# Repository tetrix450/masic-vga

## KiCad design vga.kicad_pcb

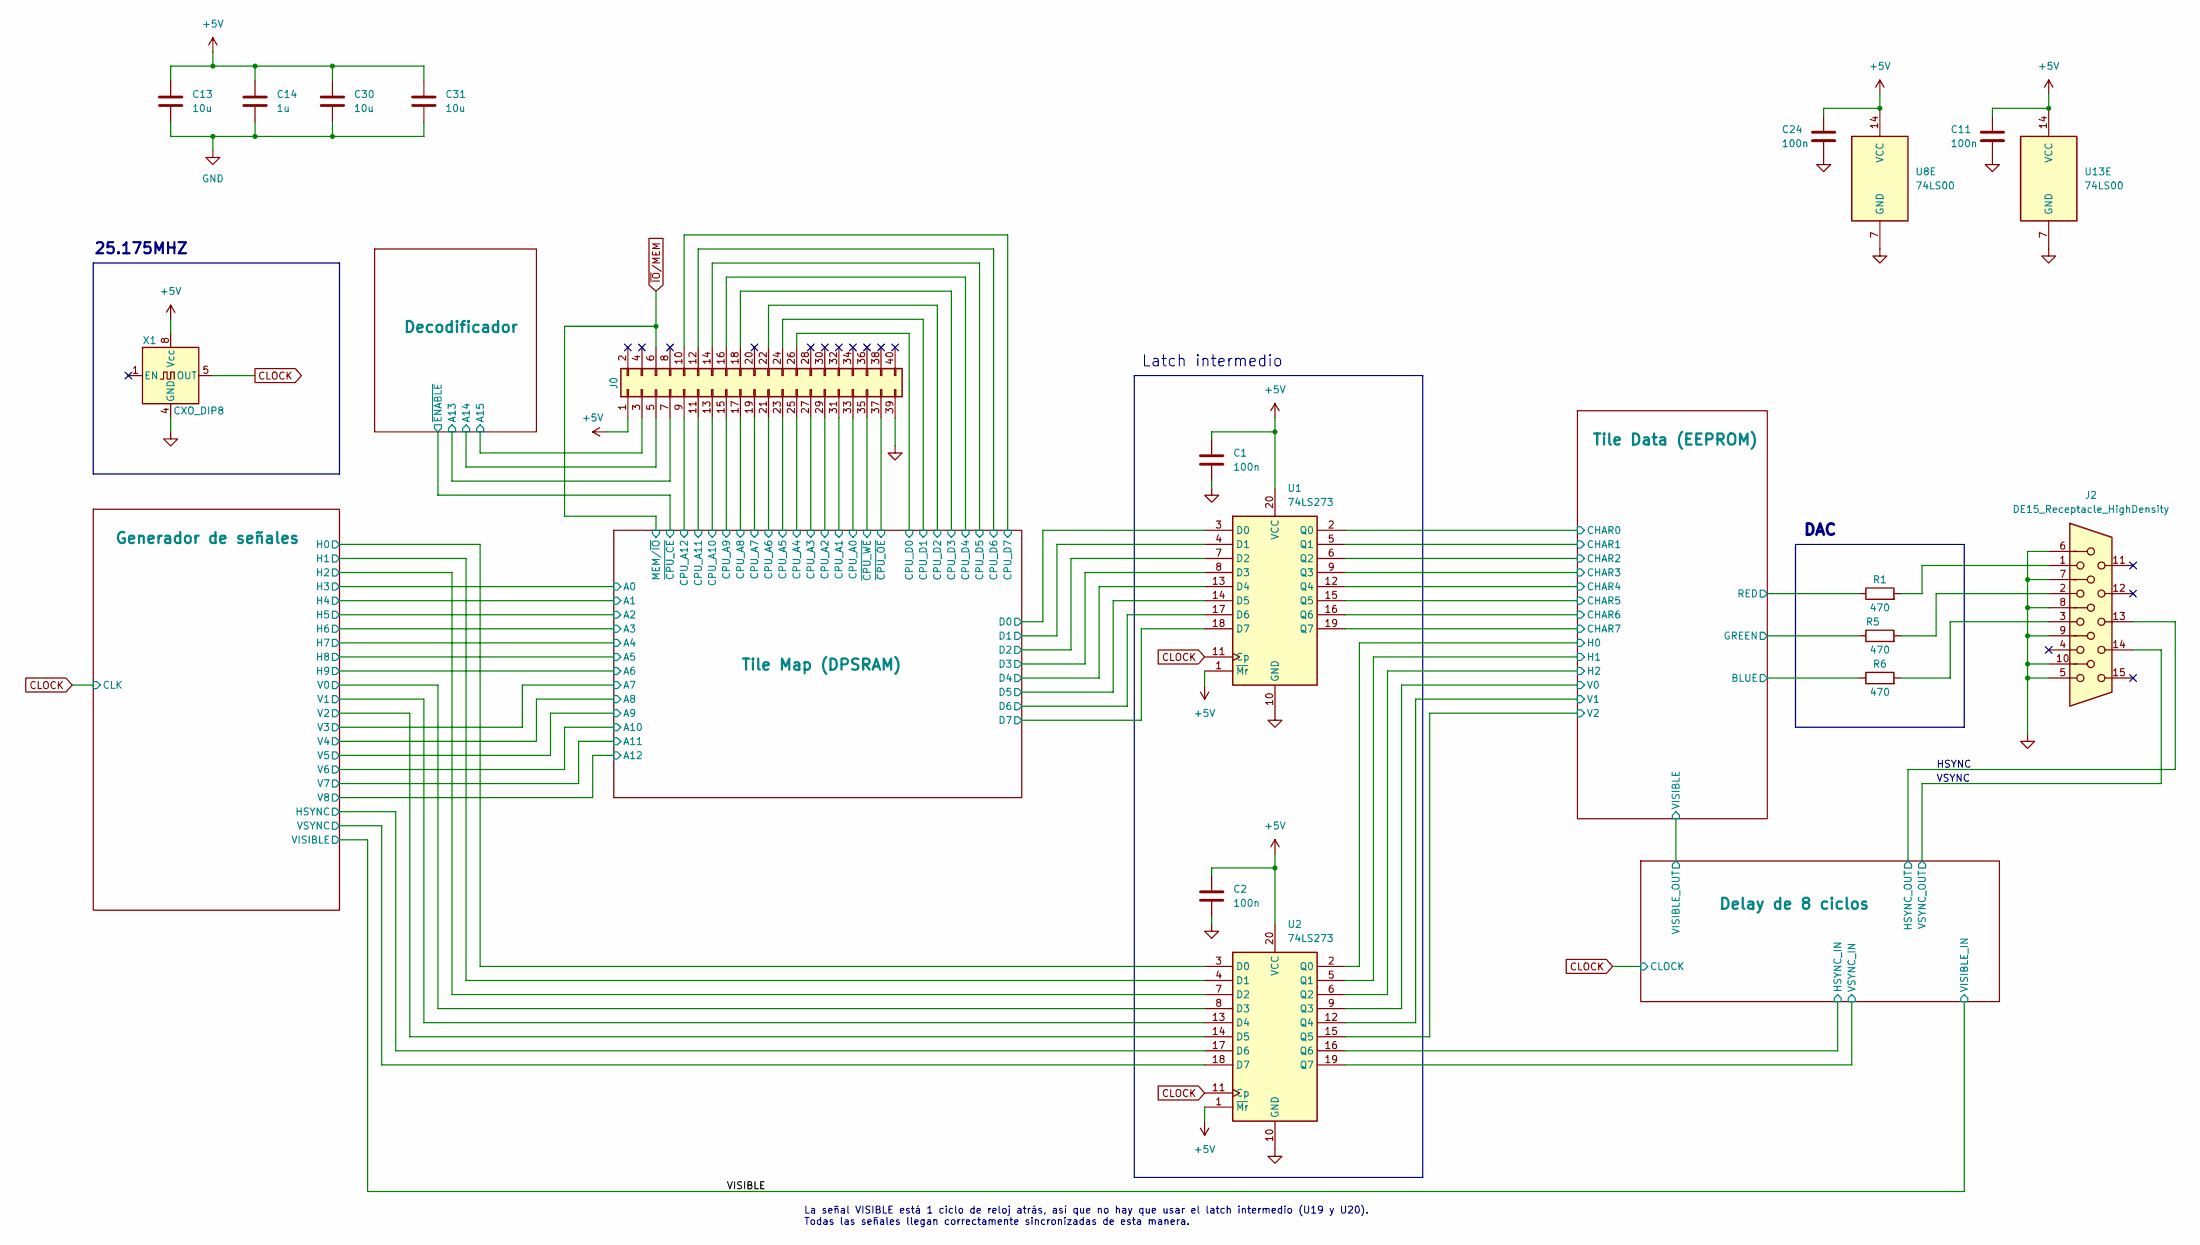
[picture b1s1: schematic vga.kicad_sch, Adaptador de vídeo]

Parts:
C1, C2, C11, C24: 100n; C_Disc_7.62mm
C13, C30, C31: 10u; C_Radial_D6.3mm_H5.0mm_P2.50mm
C14: 1u; C_Radial_D6.3mm_H5.0mm_P2.50mm
J0: Conn_02x20_Counter_Clockwise; PinSocket_2x20_P2.54mm_Vertical
J2: DE15_Receptacle_HighDensity; DSUB-15-HD_Female_Horizontal_P2.29x2.54mm_EdgePinOffset9.40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
R1, R5, R6: 470; R_Axial_DIN0207_L6.3mm_D2.5mm_P7.62mm_Horizontal
U1, U2: 74LS273; DIP-20_W7.62mm
U8, U13: 74LS00; DIP-14_W7.62mm
X1: CXO_DIP8; Oscillator_DIP-8

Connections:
+5V: C1.1, C2.1, C11.1, C13.1, C14.1, C24.1, C30.1, C31.1, U1.1 (~Mr), U1.20 (VCC), U2.1 (~Mr), U2.20 (VCC), U8.14 (VCC), U13.14 (VCC), X1.8 (Vcc); also elsewhere on the board
/Delay de 8 ciclos/HSYNC_IN: U2.16 (Q6); also elsewhere on the board
/Delay de 8 ciclos/HSYNC_OUT: J2.13; also elsewhere on the board
/Delay de 8 ciclos/VSYNC_IN: U2.19 (Q7); also elsewhere on the board
/Delay de 8 ciclos/VSYNC_OUT: J2.14; also elsewhere on the board
/Generador de señales/H0: U2.3 (D0); also elsewhere on the board
/Generador de señales/H1: U2.4 (D1); also elsewhere on the board
/Generador de señales/H2: U2.7 (D2); also elsewhere on the board
/Generador de señales/HSYNC: U2.17 (D6); also elsewhere on the board
/Generador de señales/HSYNC LATCH/Q: U8.8, U8.12; also elsewhere on the board
/Generador de señales/HSYNC LATCH/~Q: U8.10, U8.11; also elsewhere on the board
/Generador de señales/HSYNC LATCH/~R: U8.13; also elsewhere on the board
/Generador de señales/HSYNC LATCH/~S: U8.9; also elsewhere on the board
/Generador de señales/V0: U2.8 (D3); also elsewhere on the board
/Generador de señales/V1: U2.13 (D4); also elsewhere on the board
/Generador de señales/V2: U2.14 (D5); also elsewhere on the board
/Generador de señales/VSYNC: U2.18 (D7); also elsewhere on the board
/Generador de señales/VSYNC_LATCH/Q: U13.8, U13.12; also elsewhere on the board
/Generador de señales/VSYNC_LATCH/~Q: U13.10, U13.11; also elsewhere on the board
/Generador de señales/VSYNC_LATCH/~R: U13.13; also elsewhere on the board
/Generador de señales/VSYNC_LATCH/~S: U13.9; also elsewhere on the board
/Tile Data (EEPROM)/BLUE: R6.1; also elsewhere on the board
/Tile Data (EEPROM)/CHAR0: U1.2 (Q0); also elsewhere on the board
/Tile Data (EEPROM)/CHAR1: U1.5 (Q1); also elsewhere on the board
/Tile Data (EEPROM)/CHAR2: U1.6 (Q2); also elsewhere on the board
/Tile Data (EEPROM)/CHAR3: U1.9 (Q3); also elsewhere on the board
/Tile Data (EEPROM)/CHAR4: U1.12 (Q4); also elsewhere on the board
/Tile Data (EEPROM)/CHAR5: U1.15 (Q5); also elsewhere on the board
/Tile Data (EEPROM)/CHAR6: U1.16 (Q6); also elsewhere on the board
/Tile Data (EEPROM)/CHAR7: U1.19 (Q7); also elsewhere on the board
/Tile Data (EEPROM)/GREEN: R5.1; also elsewhere on the board
/Tile Data (EEPROM)/H0: U2.2 (Q0); also elsewhere on the board
/Tile Data (EEPROM)/H1: U2.5 (Q1); also elsewhere on the board
/Tile Data (EEPROM)/H2: U2.6 (Q2); also elsewhere on the board
/Tile Data (EEPROM)/RED: R1.1; also elsewhere on the board
/Tile Data (EEPROM)/V0: U2.9 (Q3); also elsewhere on the board
/Tile Data (EEPROM)/V1: U2.12 (Q4); also elsewhere on the board
/Tile Data (EEPROM)/V2: U2.15 (Q5); also elsewhere on the board
/Tile Map (DPSRAM)/D0: U1.3 (D0); also elsewhere on the board
/Tile Map (DPSRAM)/D1: U1.4 (D1); also elsewhere on the board
/Tile Map (DPSRAM)/D2: U1.7 (D2); also elsewhere on the board
/Tile Map (DPSRAM)/D3: U1.8 (D3); also elsewhere on the board
/Tile Map (DPSRAM)/D4: U1.13 (D4); also elsewhere on the board
/Tile Map (DPSRAM)/D5: U1.14 (D5); also elsewhere on the board
/Tile Map (DPSRAM)/D6: U1.17 (D6); also elsewhere on the board
/Tile Map (DPSRAM)/D7: U1.18 (D7); also elsewhere on the board
CLOCK: U1.11 (Cp), U2.11 (Cp), X1.5 (OUT); also elsewhere on the board
GND: C1.2, C2.2, C11.2, C13.2, C14.2, C24.2, C30.2, C31.2, J2.5, J2.6, J2.7, J2.8, J2.9, J2.10, U1.10 (GND), U2.10 (GND), U8.7 (GND), U13.7 (GND), X1.4 (GND); also elsewhere on the board
unnamed: J2.1, R1.2
unnamed: J2.2, R5.2
unnamed: J2.3, R6.2

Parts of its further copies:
J1: Conn_02x20_Counter_Clockwise; PinSocket_2x20_P2.54mm_Vertical

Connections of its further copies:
+5V: J1.1; also elsewhere on the board
/Decodificador/A13: J1.7; also elsewhere on the board
/Decodificador/A14: J1.5; also elsewhere on the board
/Decodificador/A15: J1.3; also elsewhere on the board
/Tile Map (DPSRAM)/CPU_A0: J1.33; also elsewhere on the board
/Tile Map (DPSRAM)/CPU_A1: J1.31; also elsewhere on the board
/Tile Map (DPSRAM)/CPU_A2: J1.29; also elsewhere on the board
/Tile Map (DPSRAM)/CPU_A3: J1.27; also elsewhere on the board
/Tile Map (DPSRAM)/CPU_A4: J1.25; also elsewhere on the board
/Tile Map (DPSRAM)/CPU_A5: J1.23; also elsewhere on the board
/Tile Map (DPSRAM)/CPU_A6: J1.21; also elsewhere on the board
/Tile Map (DPSRAM)/CPU_A7: J1.19; also elsewhere on the board
/Tile Map (DPSRAM)/CPU_A8: J1.17; also elsewhere on the board
/Tile Map (DPSRAM)/CPU_A9: J1.15; also elsewhere on the board
/Tile Map (DPSRAM)/CPU_A10: J1.13; also elsewhere on the board
/Tile Map (DPSRAM)/CPU_A11: J1.11; also elsewhere on the board
/Tile Map (DPSRAM)/CPU_A12: J1.9; also elsewhere on the board
/Tile Map (DPSRAM)/CPU_D0: J1.26; also elsewhere on the board
/Tile Map (DPSRAM)/CPU_D1: J1.24; also elsewhere on the board
/Tile Map (DPSRAM)/CPU_D2: J1.22; also elsewhere on the board
/Tile Map (DPSRAM)/CPU_D3: J1.18; also elsewhere on the board
/Tile Map (DPSRAM)/CPU_D4: J1.16; also elsewhere on the board
/Tile Map (DPSRAM)/CPU_D5: J1.14; also elsewhere on the board
/Tile Map (DPSRAM)/CPU_D6: J1.12; also elsewhere on the board
/Tile Map (DPSRAM)/CPU_D7: J1.10; also elsewhere on the board
/Tile Map (DPSRAM)/~CPU_OE: J1.37; also elsewhere on the board
/Tile Map (DPSRAM)/~CPU_WE: J1.35; also elsewhere on the board
GND: J1.39; also elsewhere on the board
~IO/MEM: J1.6; also elsewhere on the board

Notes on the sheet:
25.175MHZ
Latch intermedio
HSYNC
VSYNC
DAC
La señal VISIBLE está 1 ciclo de reloj atrás, así que no hay que usar el latch intermedio (U19 y U20). Todas las señales llegan correctamente sincronizadas de esta manera.

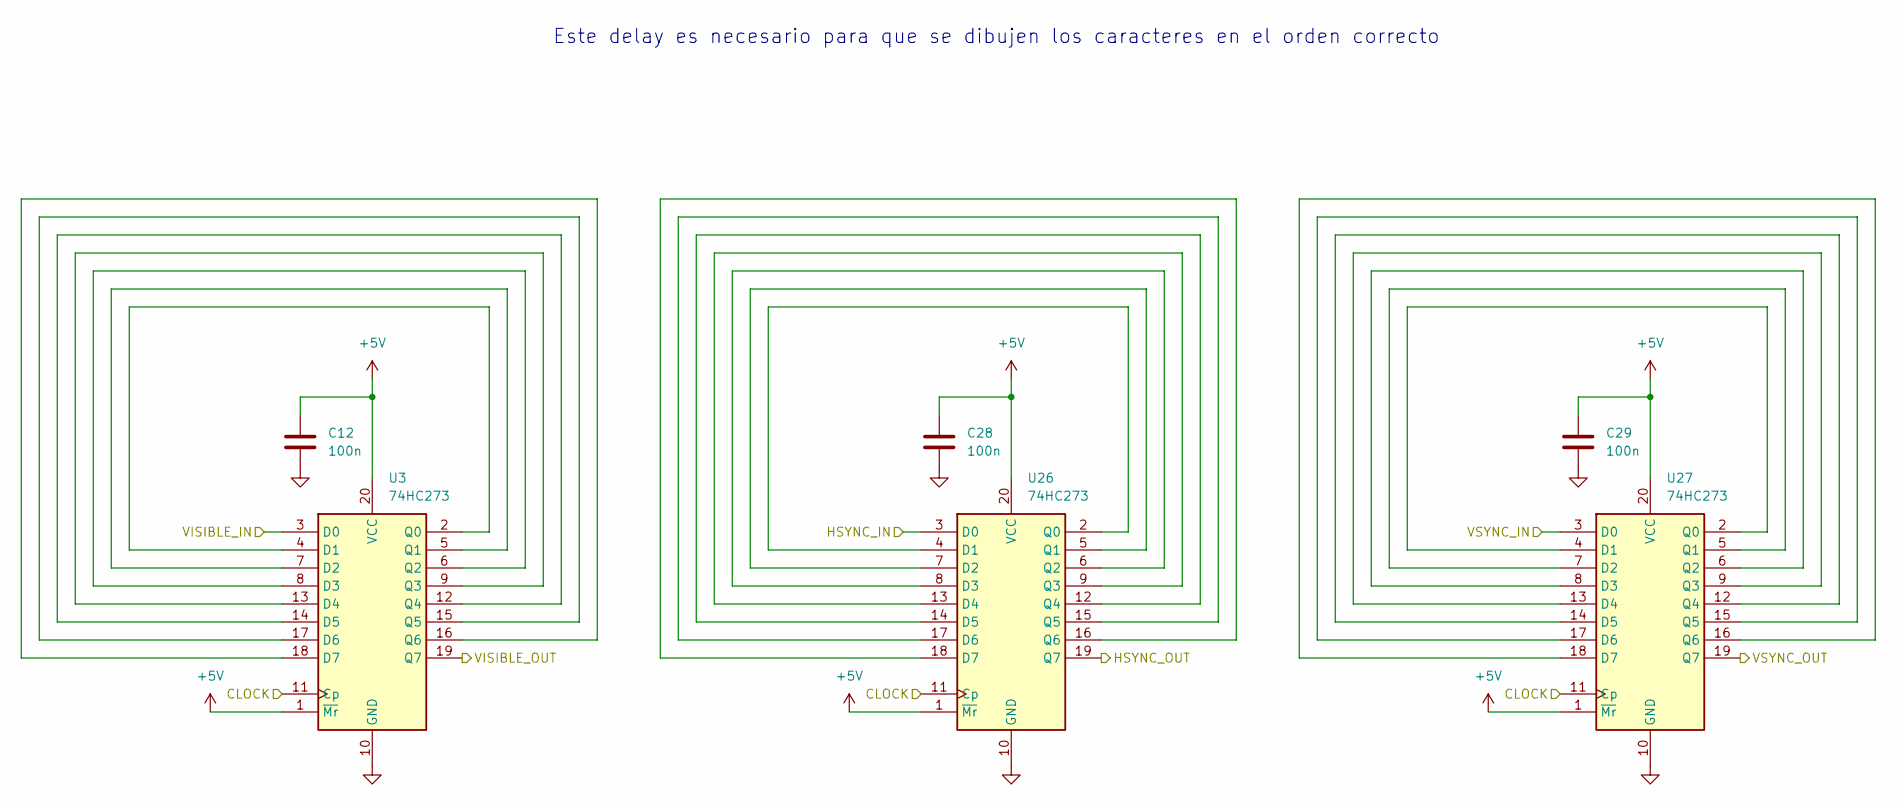
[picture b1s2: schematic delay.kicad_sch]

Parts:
C12, C28, C29: 100n; C_Disc_7.62mm
U3, U26, U27: 74HC273; DIP-20_W7.62mm

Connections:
+5V: C12.1, C28.1, C29.1, U3.1 (~Mr), U3.20 (VCC), U26.1 (~Mr), U26.20 (VCC), U27.1 (~Mr), U27.20 (VCC); also elsewhere on the board
/Delay de 8 ciclos/HSYNC_IN: U26.3 (D0); also elsewhere on the board
/Delay de 8 ciclos/HSYNC_OUT: U26.19 (Q7); also elsewhere on the board
/Delay de 8 ciclos/VISIBLE_OUT: U3.19 (Q7); also elsewhere on the board
/Delay de 8 ciclos/VSYNC_IN: U27.3 (D0); also elsewhere on the board
/Delay de 8 ciclos/VSYNC_OUT: U27.19 (Q7); also elsewhere on the board
/VISIBLE: U3.3 (D0); also elsewhere on the board
CLOCK: U3.11 (Cp), U26.11 (Cp), U27.11 (Cp); also elsewhere on the board
GND: C12.2, C28.2, C29.2, U3.10 (GND), U26.10 (GND), U27.10 (GND); also elsewhere on the board
unnamed: U3.2 (Q0), U3.4 (D1)
unnamed: U3.5 (Q1), U3.7 (D2)
unnamed: U3.6 (Q2), U3.8 (D3)
unnamed: U3.9 (Q3), U3.13 (D4)
unnamed: U3.12 (Q4), U3.14 (D5)
unnamed: U3.15 (Q5), U3.17 (D6)
unnamed: U3.16 (Q6), U3.18 (D7)
unnamed: U26.2 (Q0), U26.4 (D1)
unnamed: U26.5 (Q1), U26.7 (D2)
unnamed: U26.6 (Q2), U26.8 (D3)
unnamed: U26.9 (Q3), U26.13 (D4)
unnamed: U26.12 (Q4), U26.14 (D5)
unnamed: U26.15 (Q5), U26.17 (D6)
unnamed: U26.16 (Q6), U26.18 (D7)
unnamed: U27.2 (Q0), U27.4 (D1)
unnamed: U27.5 (Q1), U27.7 (D2)
unnamed: U27.6 (Q2), U27.8 (D3)
unnamed: U27.9 (Q3), U27.13 (D4)
unnamed: U27.12 (Q4), U27.14 (D5)
unnamed: U27.15 (Q5), U27.17 (D6)
unnamed: U27.16 (Q6), U27.18 (D7)

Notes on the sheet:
Este delay es necesario para que se dibujen los caracteres en el orden correcto

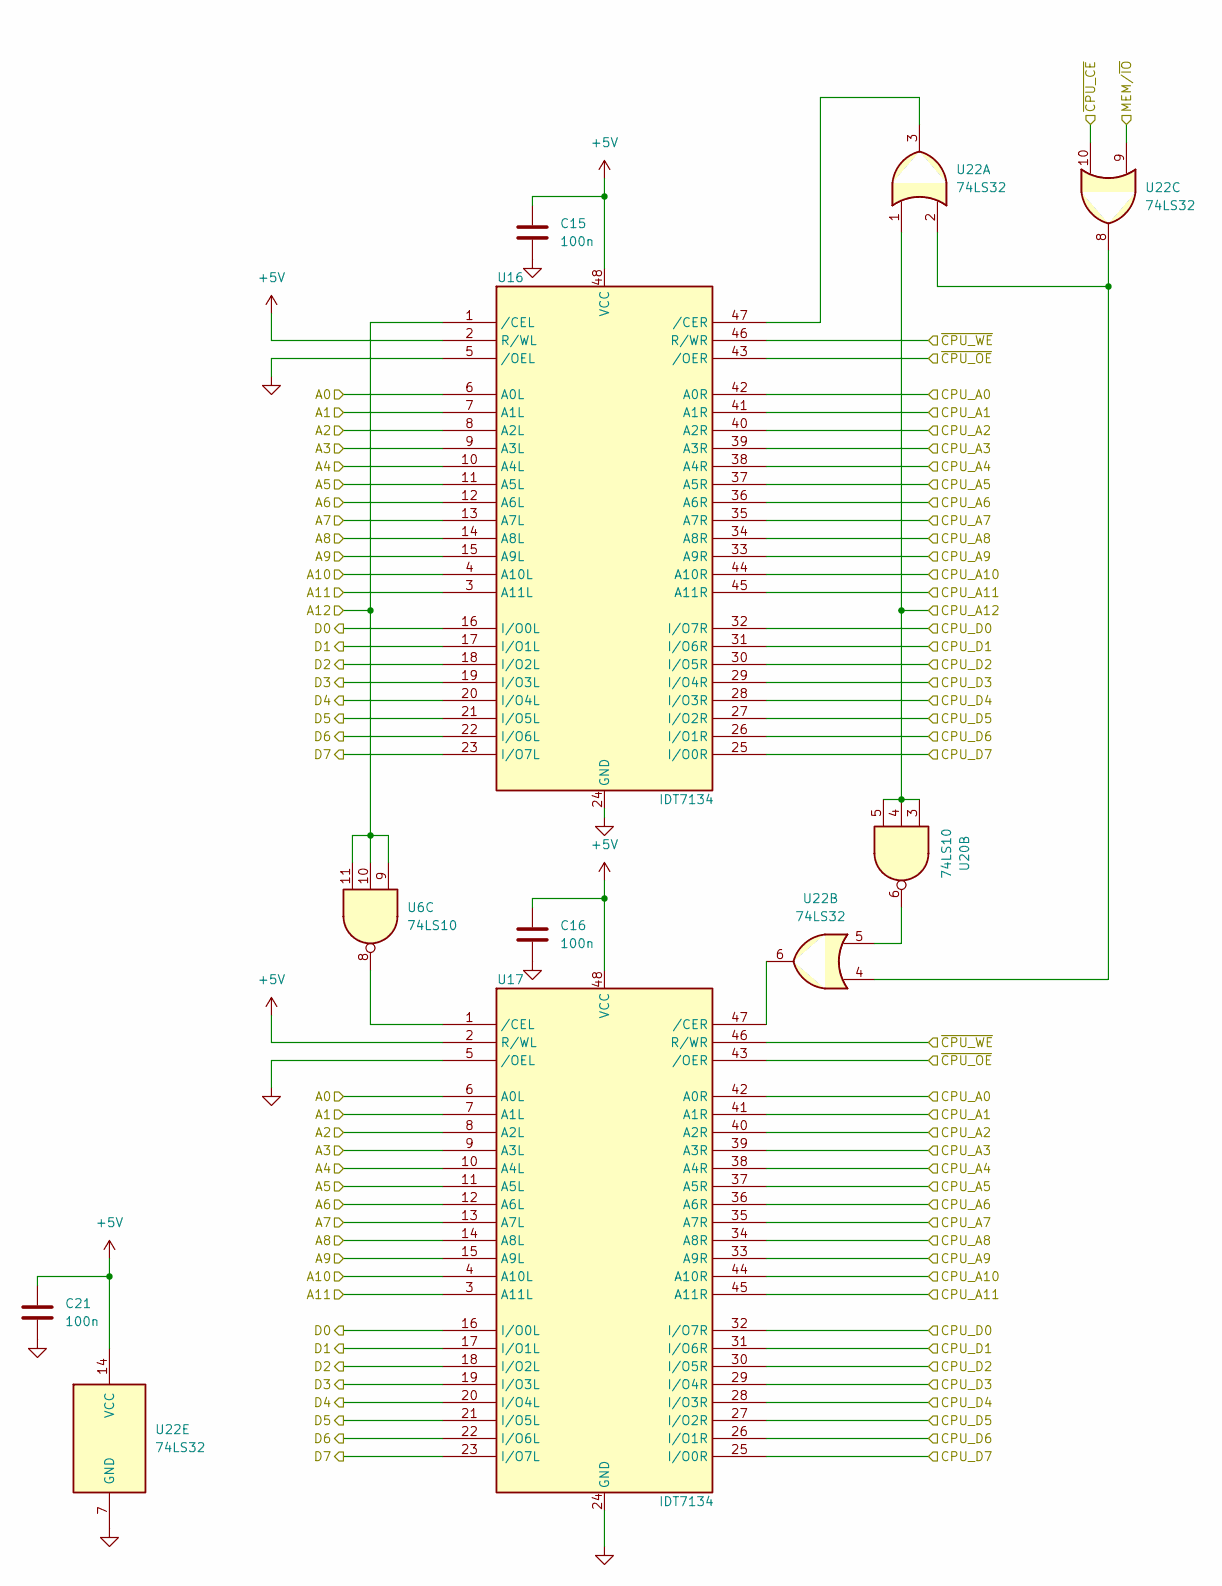
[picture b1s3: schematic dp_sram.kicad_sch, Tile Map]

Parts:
C15, C16, C21: 100n; C_Disc_7.62mm
U6, U20: 74LS10; DIP-14_W7.62mm
U16, U17: IDT7134; DIP-48_W15.24mm
U22: 74LS32; DIP-14_W7.62mm

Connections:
+5V: C15.1, C16.1, C21.1, U16.2 (R/WL), U16.48 (VCC), U17.2 (R/WL), U17.48 (VCC), U22.14 (VCC); also elsewhere on the board
/Decodificador/~ENABLE: U22.10; also elsewhere on the board
/Generador de señales/H3: U16.6 (A0L), U17.6 (A0L); also elsewhere on the board
/Generador de señales/H4: U16.7 (A1L), U17.7 (A1L); also elsewhere on the board
/Generador de señales/H5: U16.8 (A2L), U17.8 (A2L); also elsewhere on the board
/Generador de señales/H6: U16.9 (A3L), U17.9 (A3L); also elsewhere on the board
/Generador de señales/H7: U16.10 (A4L), U17.10 (A4L); also elsewhere on the board
/Generador de señales/H8: U16.11 (A5L), U17.11 (A5L); also elsewhere on the board
/Generador de señales/H9: U16.12 (A6L), U17.12 (A6L); also elsewhere on the board
/Generador de señales/V3: U16.13 (A7L), U17.13 (A7L); also elsewhere on the board
/Generador de señales/V4: U16.14 (A8L), U17.14 (A8L); also elsewhere on the board
/Generador de señales/V5: U16.15 (A9L), U17.15 (A9L); also elsewhere on the board
/Generador de señales/V6: U16.4 (A10L), U17.4 (A10L); also elsewhere on the board
/Generador de señales/V7: U16.3 (A11L), U17.3 (A11L); also elsewhere on the board
/Generador de señales/V8: U6.9, U6.10, U6.11, U16.1 (/CEL); also elsewhere on the board
/Tile Map (DPSRAM)/CPU_A0: U16.42 (A0R), U17.42 (A0R); also elsewhere on the board
/Tile Map (DPSRAM)/CPU_A1: U16.41 (A1R), U17.41 (A1R); also elsewhere on the board
/Tile Map (DPSRAM)/CPU_A2: U16.40 (A2R), U17.40 (A2R); also elsewhere on the board
/Tile Map (DPSRAM)/CPU_A3: U16.39 (A3R), U17.39 (A3R); also elsewhere on the board
/Tile Map (DPSRAM)/CPU_A4: U16.38 (A4R), U17.38 (A4R); also elsewhere on the board
/Tile Map (DPSRAM)/CPU_A5: U16.37 (A5R), U17.37 (A5R); also elsewhere on the board
/Tile Map (DPSRAM)/CPU_A6: U16.36 (A6R), U17.36 (A6R); also elsewhere on the board
/Tile Map (DPSRAM)/CPU_A7: U16.35 (A7R), U17.35 (A7R); also elsewhere on the board
/Tile Map (DPSRAM)/CPU_A8: U16.34 (A8R), U17.34 (A8R); also elsewhere on the board
/Tile Map (DPSRAM)/CPU_A9: U16.33 (A9R), U17.33 (A9R); also elsewhere on the board
/Tile Map (DPSRAM)/CPU_A10: U16.44 (A10R), U17.44 (A10R); also elsewhere on the board
/Tile Map (DPSRAM)/CPU_A11: U16.45 (A11R), U17.45 (A11R); also elsewhere on the board
/Tile Map (DPSRAM)/CPU_A12: U20.3, U20.4, U20.5, U22.1; also elsewhere on the board
/Tile Map (DPSRAM)/CPU_D0: U16.32 (I/O7R), U17.32 (I/O7R); also elsewhere on the board
/Tile Map (DPSRAM)/CPU_D1: U16.31 (I/O6R), U17.31 (I/O6R); also elsewhere on the board
/Tile Map (DPSRAM)/CPU_D2: U16.30 (I/O5R), U17.30 (I/O5R); also elsewhere on the board
/Tile Map (DPSRAM)/CPU_D3: U16.29 (I/O4R), U17.29 (I/O4R); also elsewhere on the board
/Tile Map (DPSRAM)/CPU_D4: U16.28 (I/O3R), U17.28 (I/O3R); also elsewhere on the board
/Tile Map (DPSRAM)/CPU_D5: U16.27 (I/O2R), U17.27 (I/O2R); also elsewhere on the board
/Tile Map (DPSRAM)/CPU_D6: U16.26 (I/O1R), U17.26 (I/O1R); also elsewhere on the board
/Tile Map (DPSRAM)/CPU_D7: U16.25 (I/O0R), U17.25 (I/O0R); also elsewhere on the board
/Tile Map (DPSRAM)/D0: U16.16 (I/O0L), U17.16 (I/O0L); also elsewhere on the board
/Tile Map (DPSRAM)/D1: U16.17 (I/O1L), U17.17 (I/O1L); also elsewhere on the board
/Tile Map (DPSRAM)/D2: U16.18 (I/O2L), U17.18 (I/O2L); also elsewhere on the board
/Tile Map (DPSRAM)/D3: U16.19 (I/O3L), U17.19 (I/O3L); also elsewhere on the board
/Tile Map (DPSRAM)/D4: U16.20 (I/O4L), U17.20 (I/O4L); also elsewhere on the board
/Tile Map (DPSRAM)/D5: U16.21 (I/O5L), U17.21 (I/O5L); also elsewhere on the board
/Tile Map (DPSRAM)/D6: U16.22 (I/O6L), U17.22 (I/O6L); also elsewhere on the board
/Tile Map (DPSRAM)/D7: U16.23 (I/O7L), U17.23 (I/O7L); also elsewhere on the board
/Tile Map (DPSRAM)/~CPU_OE: U16.43 (/OER), U17.43 (/OER); also elsewhere on the board
/Tile Map (DPSRAM)/~CPU_WE: U16.46 (R/WR), U17.46 (R/WR); also elsewhere on the board
GND: C15.2, C16.2, C21.2, U16.5 (/OEL), U16.24 (GND), U17.5 (/OEL), U17.24 (GND), U22.7 (GND); also elsewhere on the board
unnamed: U16.47 (/CER), U22.3
unnamed: U6.8, U17.1 (/CEL)
unnamed: U17.47 (/CER), U22.6
unnamed: U20.6, U22.5
unnamed: U22.2, U22.4, U22.8
~IO/MEM: U22.9; also elsewhere on the board

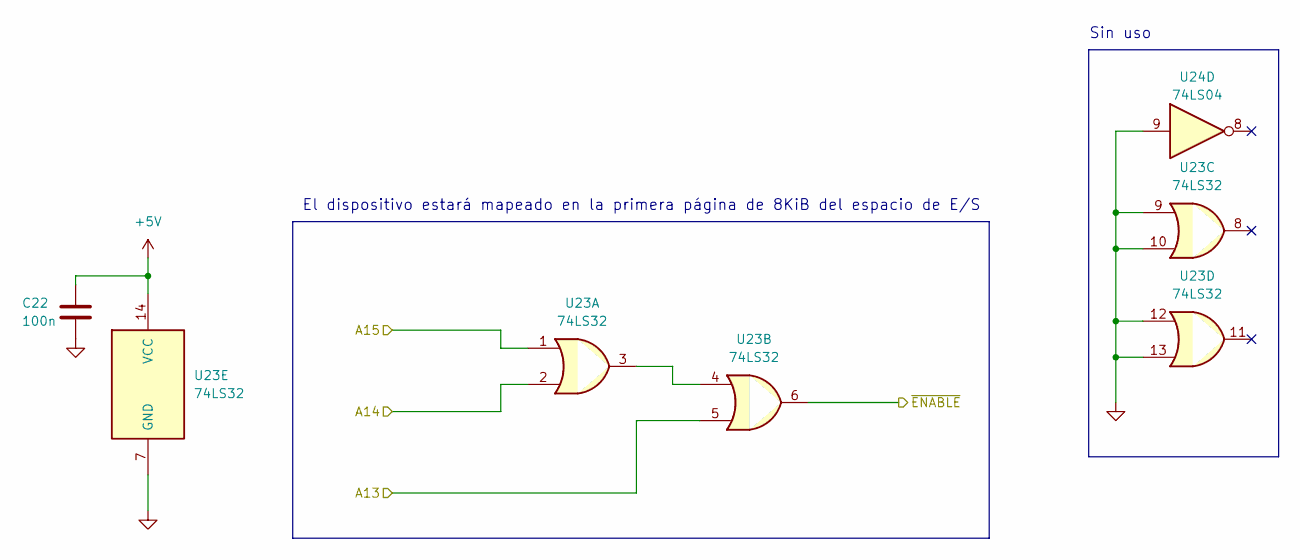
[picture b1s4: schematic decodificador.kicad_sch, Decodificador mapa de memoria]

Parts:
C22: 100n; C_Disc_7.62mm
U23: 74LS32; DIP-14_W7.62mm
U24: 74LS04; DIP-14_W7.62mm

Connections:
+5V: C22.1, U23.14 (VCC); also elsewhere on the board
/Decodificador/A13: U23.5; also elsewhere on the board
/Decodificador/A14: U23.2; also elsewhere on the board
/Decodificador/A15: U23.1; also elsewhere on the board
/Decodificador/~ENABLE: U23.6; also elsewhere on the board
GND: C22.2, U23.7 (GND), U23.9, U23.10, U23.12, U23.13, U24.9; also elsewhere on the board
unnamed: U23.3, U23.4

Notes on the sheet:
Sin uso
El dispositivo estará mapeado en la primera página de 8KiB del espacio de E/S

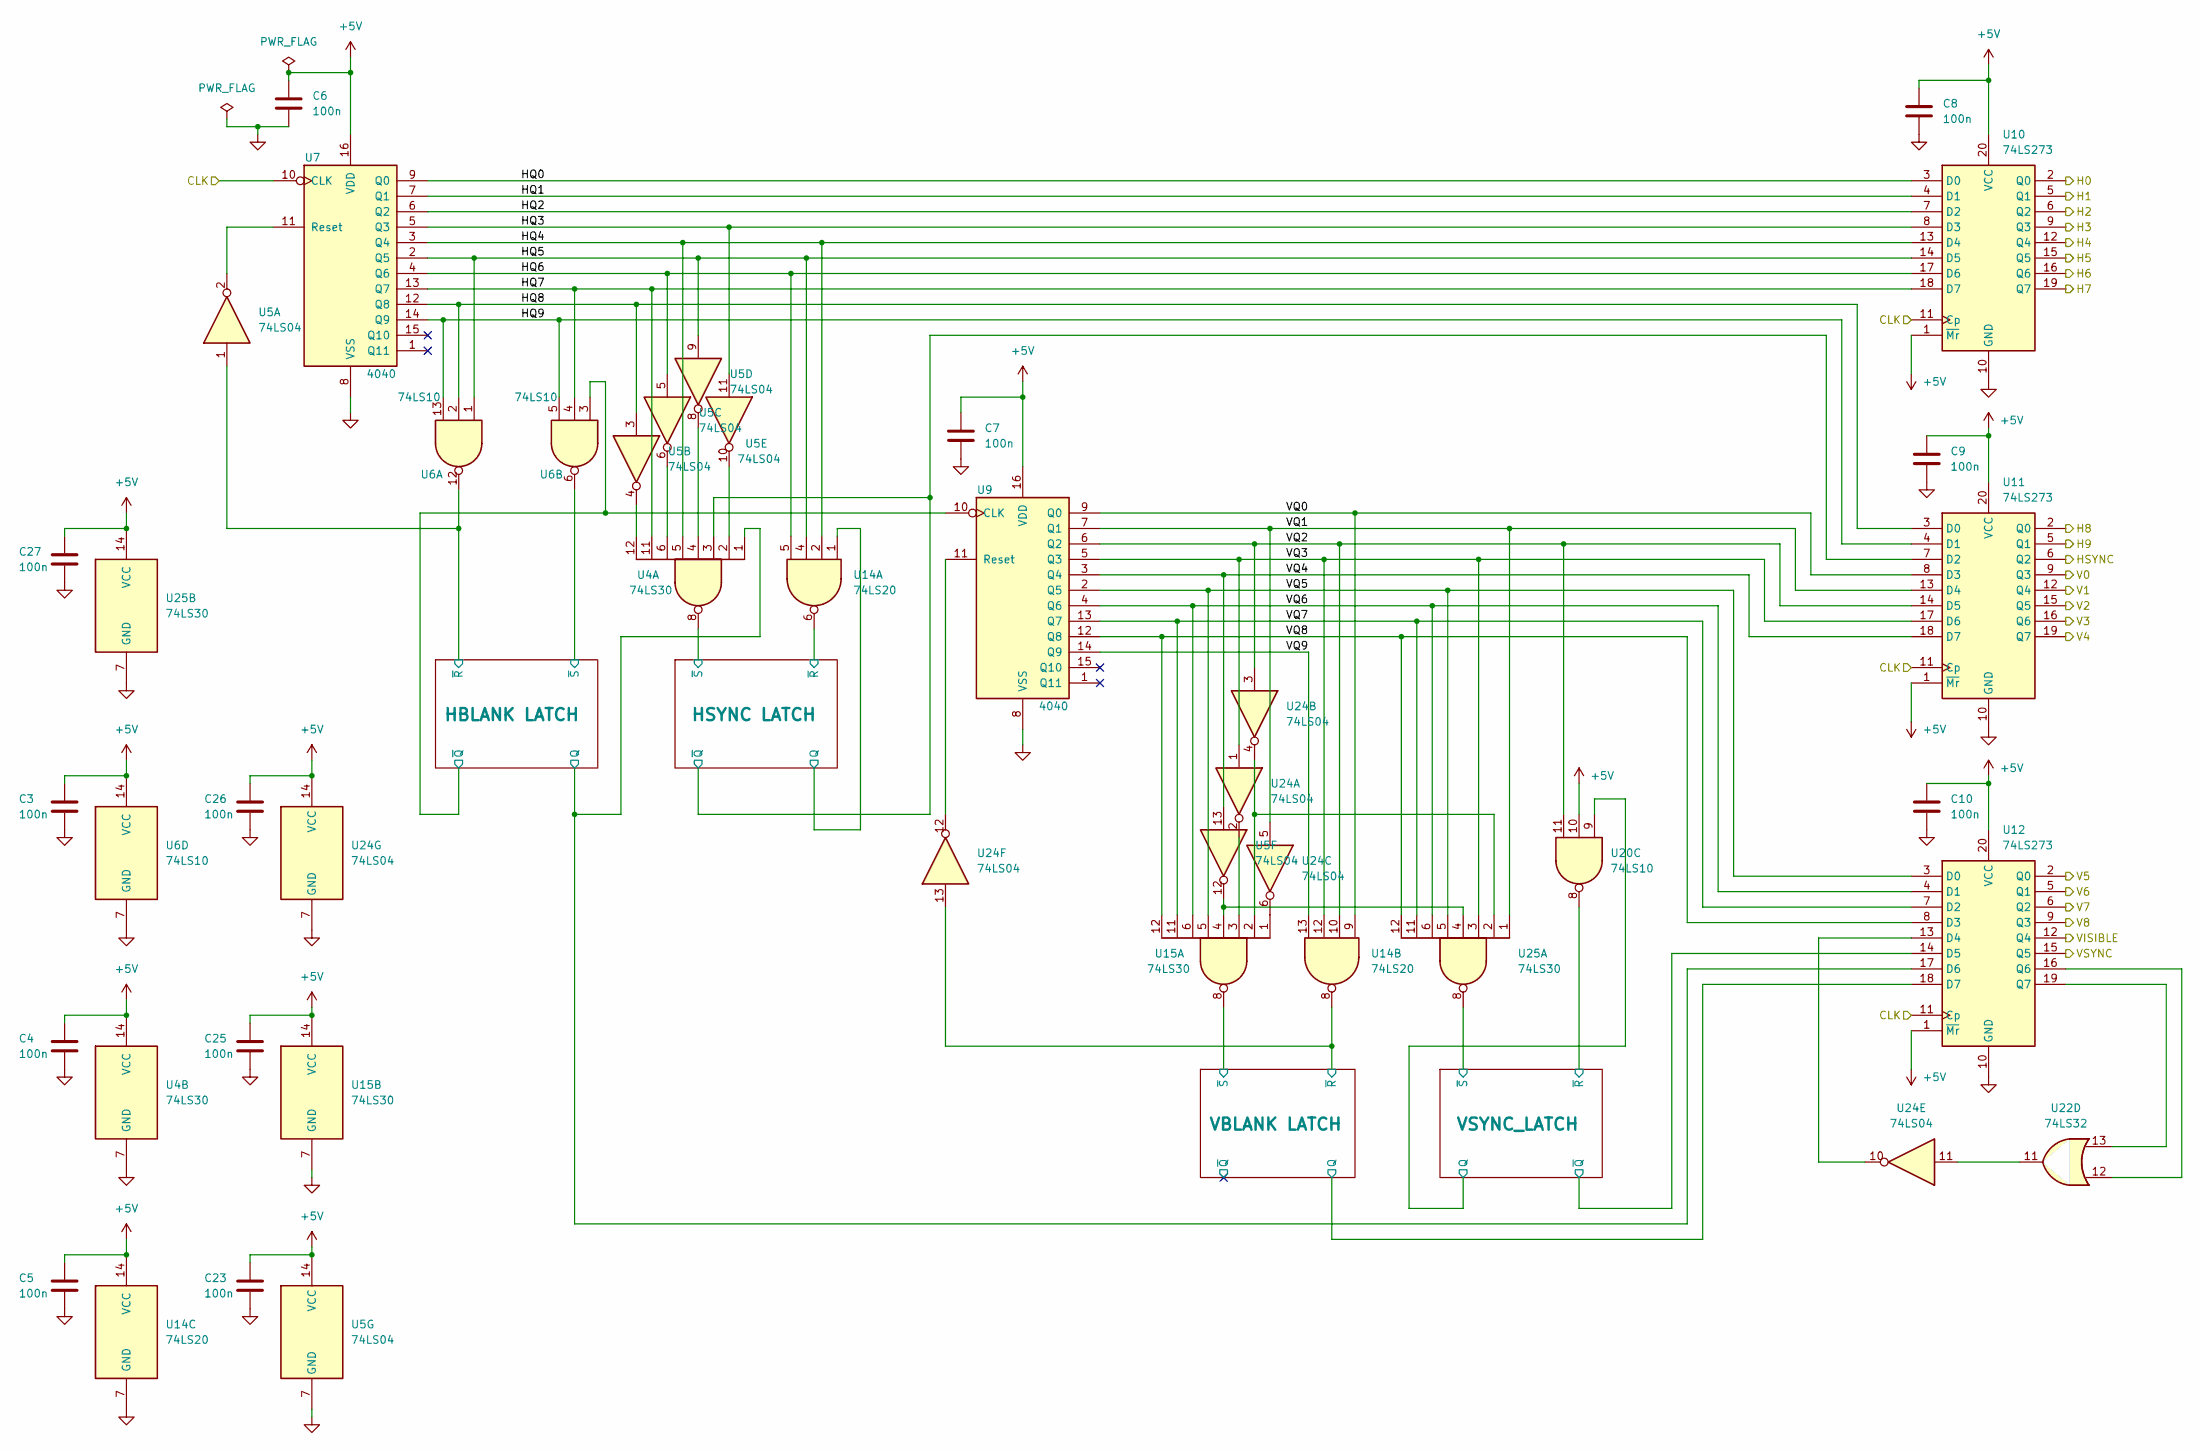
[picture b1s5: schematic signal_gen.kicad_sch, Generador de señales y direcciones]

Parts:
C3, C4, C5, C6, C7, C8, C9, C10, C23, C25, C26, C27: 100n; C_Disc_7.62mm
U4, U15, U25: 74LS30; DIP-14_W7.62mm
U5, U24: 74LS04; DIP-14_W7.62mm
U6, U20: 74LS10; DIP-14_W7.62mm
U7, U9: 4040; DIP-16_W7.62mm
U10, U11, U12: 74LS273; DIP-20_W7.62mm
U14: 74LS20; DIP-14_W7.62mm
U22: 74LS32; DIP-14_W7.62mm

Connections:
+5V: C3.1, C4.1, C5.1, C6.1, C7.1, C8.1, C9.1, C10.1, C23.1, C25.1, C26.1, C27.1, U4.14 (VCC), U5.14 (VCC), U6.14 (VCC), U7.16 (VDD), U9.16 (VDD), U10.1 (~Mr), U10.20 (VCC), U11.1 (~Mr), U11.20 (VCC), U12.1 (~Mr), U12.20 (VCC), U14.14 (VCC), U15.14 (VCC), U20.10, U24.14 (VCC), U25.14 (VCC); also elsewhere on the board
/Generador de señales/H0: U10.2 (Q0); also elsewhere on the board
/Generador de señales/H1: U10.5 (Q1); also elsewhere on the board
/Generador de señales/H2: U10.6 (Q2); also elsewhere on the board
/Generador de señales/H3: U10.9 (Q3); also elsewhere on the board
/Generador de señales/H4: U10.12 (Q4); also elsewhere on the board
/Generador de señales/H5: U10.15 (Q5); also elsewhere on the board
/Generador de señales/H6: U10.16 (Q6); also elsewhere on the board
/Generador de señales/H7: U10.19 (Q7); also elsewhere on the board
/Generador de señales/H8: U11.2 (Q0); also elsewhere on the board
/Generador de señales/H9: U11.5 (Q1); also elsewhere on the board
/Generador de señales/HBLANK LATCH/Q: U4.1, U12.17 (D6); also elsewhere on the board
/Generador de señales/HBLANK LATCH/~Q: U6.3, U9.10 (CLK); also elsewhere on the board
/Generador de señales/HBLANK LATCH/~R: U5.1, U6.12; also elsewhere on the board
/Generador de señales/HBLANK LATCH/~S: U6.6; also elsewhere on the board
/Generador de señales/HQ0: U7.9 (Q0), U10.3 (D0)
/Generador de señales/HQ1: U7.7 (Q1), U10.4 (D1)
/Generador de señales/HQ2: U7.6 (Q2), U10.7 (D2)
/Generador de señales/HQ3: U5.11, U7.5 (Q3), U10.8 (D3)
/Generador de señales/HQ4: U4.5, U7.3 (Q4), U10.13 (D4), U14.2
/Generador de señales/HQ5: U5.9, U6.1, U7.2 (Q5), U10.14 (D5), U14.4
/Generador de señales/HQ6: U5.5, U7.4 (Q6), U10.17 (D6), U14.5
/Generador de señales/HQ7: U4.11, U6.4, U7.13 (Q7), U10.18 (D7)
/Generador de señales/HQ8: U5.3, U6.2, U7.12 (Q8), U11.3 (D0)
/Generador de señales/HQ9: U6.5, U6.13, U7.14 (Q9), U11.4 (D1)
/Generador de señales/HSYNC: U11.6 (Q2); also elsewhere on the board
/Generador de señales/HSYNC LATCH/Q: U14.1; also elsewhere on the board
/Generador de señales/HSYNC LATCH/~Q: U4.3, U11.7 (D2); also elsewhere on the board
/Generador de señales/HSYNC LATCH/~R: U14.6; also elsewhere on the board
/Generador de señales/HSYNC LATCH/~S: U4.8; also elsewhere on the board
/Generador de señales/V0: U11.9 (Q3); also elsewhere on the board
/Generador de señales/V1: U11.12 (Q4); also elsewhere on the board
/Generador de señales/V2: U11.15 (Q5); also elsewhere on the board
/Generador de señales/V3: U11.16 (Q6); also elsewhere on the board
/Generador de señales/V4: U11.19 (Q7); also elsewhere on the board
/Generador de señales/V5: U12.2 (Q0); also elsewhere on the board
/Generador de señales/V6: U12.5 (Q1); also elsewhere on the board
/Generador de señales/V7: U12.6 (Q2); also elsewhere on the board
/Generador de señales/V8: U12.9 (Q3); also elsewhere on the board
/Generador de señales/VBLANK LATCH/Q: U12.18 (D7); also elsewhere on the board
/Generador de señales/VBLANK LATCH/~R: U14.8, U24.13; also elsewhere on the board
/Generador de señales/VBLANK LATCH/~S: U15.8; also elsewhere on the board
/Generador de señales/VQ0: U9.9 (Q0), U11.8 (D3), U14.9
/Generador de señales/VQ1: U9.7 (Q1), U11.13 (D4), U24.5, U25.1
/Generador de señales/VQ2: U9.6 (Q2), U11.14 (D5), U14.10, U20.11, U24.3
/Generador de señales/VQ3: U9.5 (Q3), U11.17 (D6), U14.12, U24.1, U25.3
/Generador de señales/VQ4: U5.13, U9.3 (Q4), U11.18 (D7)
/Generador de señales/VQ5: U9.2 (Q5), U12.3 (D0), U15.5, U25.5
/Generador de señales/VQ6: U9.4 (Q6), U12.4 (D1), U15.6, U25.6
/Generador de señales/VQ7: U9.13 (Q7), U12.7 (D2), U15.11, U25.11
/Generador de señales/VQ8: U9.12 (Q8), U12.8 (D3), U15.12, U25.12
/Generador de señales/VQ9: U9.14 (Q9), U14.13
/Generador de señales/VSYNC: U12.15 (Q5); also elsewhere on the board
/Generador de señales/VSYNC_LATCH/Q: U20.9; also elsewhere on the board
/Generador de señales/VSYNC_LATCH/~Q: U12.14 (D5); also elsewhere on the board
/Generador de señales/VSYNC_LATCH/~R: U20.8; also elsewhere on the board
/Generador de señales/VSYNC_LATCH/~S: U25.8; also elsewhere on the board
/VISIBLE: U12.12 (Q4); also elsewhere on the board
CLOCK: U7.10 (CLK), U10.11 (Cp), U11.11 (Cp), U12.11 (Cp); also elsewhere on the board
GND: C3.2, C4.2, C5.2, C6.2, C7.2, C8.2, C9.2, C10.2, C23.2, C25.2, C26.2, C27.2, U4.7 (GND), U5.7 (GND), U6.7 (GND), U7.8 (VSS), U9.8 (VSS), U10.10 (GND), U11.10 (GND), U12.10 (GND), U14.7 (GND), U15.7 (GND), U24.7 (GND), U25.7 (GND); also elsewhere on the board
unnamed: U4.2, U5.10
unnamed: U4.4, U5.8
unnamed: U4.6, U5.6
unnamed: U4.12, U5.4
unnamed: U5.2, U7.11 (Reset)
unnamed: U9.11 (Reset), U24.12
unnamed: U12.13 (D4), U24.10
unnamed: U12.16 (Q6), U22.12
unnamed: U12.19 (Q7), U22.13
unnamed: U15.1, U24.6
unnamed: U15.2, U24.4, U25.2
unnamed: U15.3, U24.2
unnamed: U5.12, U15.4, U25.4
unnamed: U22.11, U24.11
